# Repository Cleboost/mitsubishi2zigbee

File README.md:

# mitsubishi2zigbee

> [!CAUTION]
> **Early development - prototype only. Not production-ready.**
>
> This project is experimental and under active development. Firmware, wiring, and Zigbee behavior may change without notice. Bugs, incomplete features, and unexpected HVAC behavior are possible.
>
> **Do not rely on this device for critical climate control.** Use at your own risk. Test thoroughly before leaving it unattended.

Zigbee gateway firmware for Mitsubishi heat pumps and air conditioners with a **CN105** service port.

An **ESP32-C6** talks to the indoor unit over UART (CN105 protocol) and exposes it as a native Zigbee HVAC thermostat - no Wi-Fi or MQTT bridge on the microcontroller.

```
Home Assistant / Zigbee coordinator  ── Zigbee ──►  ESP32-C6  ── UART ──►  Mitsubishi unit
```

Inspired by [gysmo38/mitsubishi2MQTT](https://github.com/gysmo38/mitsubishi2MQTT), but uses Zigbee clusters (`hvacThermostat` + `hvacFanCtrl`) instead of MQTT.

## Features

| Category | Details |
| --- | --- |
| **Modes** | Off, Heat, Cool, Auto, Fan only, Dry |
| **Setpoint** | 16–31 °C in 0.5 °C steps |
| **Fan speed** | Auto, Quiet (Smart), Low, Medium, High |
| **Vane** | Auto, positions 1–5, Swing |
| **Telemetry** | Room temperature (unit sensor) |
| **Status LED** (WS2812) | Fast blue - scanning · Slow blue - network found, not paired · Green pulse - paired |

## Hardware

### Supported board

- [Waveshare ESP32-C6-Zero](https://www.waveshare.com/esp32-c6-zero.htm) (or any ESP32-C6 dev board with similar pinout)
- Built with **ESP-IDF** via **PlatformIO**

### CN105 wiring

The CN105 port provides 12 V, 5 V, and 5 V logic UART lines.

| CN105 pin | Signal | ESP32-C6 | Notes |
| --- | --- | --- | --- |
| 1 | 12 V | - | Do **not** use to power the ESP |
| 2 | GND | GND | Common ground |
| 3 | 5 V | 5 V / VBUS | Powers the ESP32-C6 |
| 4 | TX (unit → ESP) | GPIO 5 (UART RX) | 5 V logic - level shifted (5 V → 3.3 V) |
| 5 | RX (unit ← ESP) | GPIO 4 (UART TX) | 3.3 V logic - level shifted (3.3 V → 5 V) |

> **Warning:** Never feed 12 V into the ESP. Power the board from the CN105 5 V pin only.

## Build and flash

### Prerequisites

- [PlatformIO](https://platformio.org/) (VS Code extension or CLI)

### Commands

```bash
cd firmware
pio run --target upload    # build and flash
pio device monitor         # serial logs (115200 baud)
```

## Zigbee pairing

1. Flash the firmware and power the board from the CN105 port.
2. Put your Zigbee coordinator into pairing mode.
3. Watch the status LED:
   - Fast blue - searching for a network
   - Slow blue - network found, waiting to join
   - Green pulse - joined successfully
4. The device advertises as **`MZ-Zigbee-C6`** (vendor: Mitsubishi).

## Zigbee2MQTT integration

> **To write** - step-by-step setup guide coming soon.

A video tutorial will cover the full Zigbee2MQTT setup (external converter, `configuration.yaml`, pairing, and Home Assistant entities). Stay tuned.

In the meantime, the external converter source is already available in [`zigbee2mqtt_converter/mitsubishi_esp32c6.js`](zigbee2mqtt_converter/mitsubishi_esp32c6.js).

## Project layout

```
mitsubishi2zigbee/
├── hardware/                  # KiCad PCB (CN105 carrier for ESP32-C6-Zero)
├── firmware/                  # ESP-IDF / PlatformIO project
│   └── src/
│       ├── main.cpp           # Zigbee endpoint + status LED
│       └── cn105.cpp          # Mitsubishi CN105 UART driver
└── zigbee2mqtt_converter/     # Optional Z2M external converter

```

## License

See repository license file.

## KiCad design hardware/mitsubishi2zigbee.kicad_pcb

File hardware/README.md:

# Hardware

KiCad PCB for a [Waveshare ESP32-C6-Zero](https://www.waveshare.com/esp32-c6-zero.htm) carrier that plugs into a Mitsubishi **CN105** service port.

| Item | Details |
| --- | --- |
| MCU footprint | `Waveshare-ESP32:Waveshare-ESP32-C6-Zero_THT` (2×9 pin headers) |
| CN105 connector | `JST:JST_PA_B05B-PASK-1_1x05_P2.00mm_Vertical_CN105` |
| Level shifting | 5 V UART from the unit → 3.3 V for the ESP |

## CN105 UART wiring (rev 1 errata)

Mitsubishi CN105 pinout (viewed from the board):

| Pin | Signal | Direction (unit) |
| --- | --- | --- |
| 4 | TX | unit → ESP (ESP must **receive** here) |
| 5 | RX | ESP → unit (ESP must **transmit** here) |

**Rev 1 PCB bug:** pins 4 and 5 were swapped at the JST connector (ESP TX was routed to unit TX pin 4, ESP RX to unit RX pin 5). Symptom: yellow LED (Zigbee OK but CN105 silent), no UART traffic - no amount of firmware fixes this.

**Fix on assembled board:** cross **only** CN105 pins **4 ↔ 5** (swap the two UART wires on the cable or at `J1`). GND / 5 V unchanged.

Fixed in `mitsubishi2zigbee.kicad_pcb` for the next fabrication run.

## Open in KiCad

```bash
kicad hardware/mitsubishi2zigbee.kicad_pro
```

Project-specific symbol and footprint libraries live in `libs/`.

## Layout

```
hardware/
├── README.md
├── schematic.png
├── mitsubishi2zigbee.kicad_pro
├── mitsubishi2zigbee.kicad_sch
├── mitsubishi2zigbee.kicad_pcb
├── fp-lib-table
├── sym-lib-table
└── libs/
    ├── JST.pretty/
    ├── Waveshare-ESP32.pretty/
    └── Waveshare-ESP32.kicad_sym
```

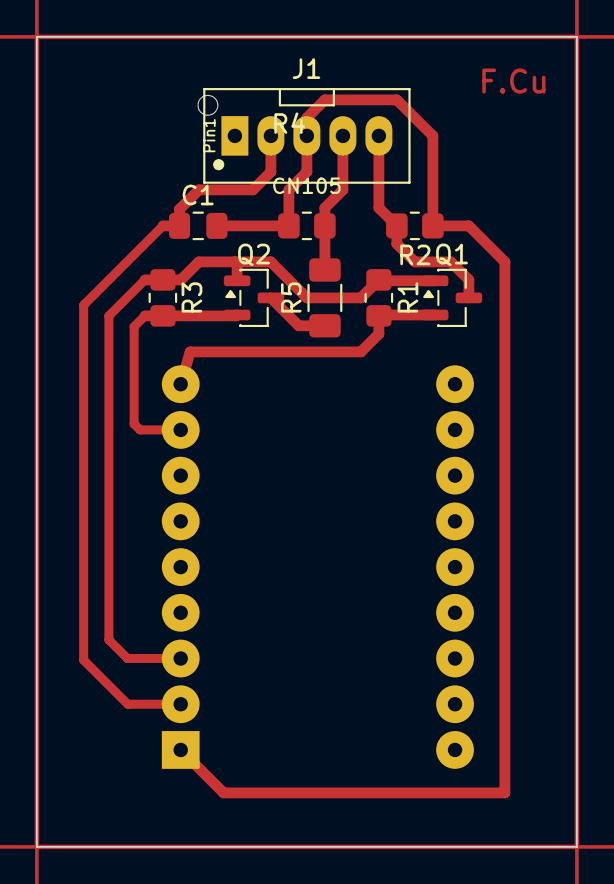
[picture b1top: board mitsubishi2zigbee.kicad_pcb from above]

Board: 2 copper layers, 30.0 x 45.0 mm, 10 parts (1 on the bottom side), 8 nets.

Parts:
C1: 10uF; C_0805_2012Metric_Pad1.18x1.45mm_HandSolder
J1: CN105; JST_PA_B05B-PASK-1_1x05_P2.00mm_Vertical_CN105
Q1, Q2: BSS138; SOT-23
R1, R2, R3, R4: 10K; R_0805_2012Metric_Pad1.20x1.40mm_HandSolder
R5: 0R; R_1206_3216Metric_Pad1.30x1.75mm_HandSolder
U1: ESP32-C6-Zero; Waveshare-ESP32-C6-Zero_THT

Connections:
+3V3: Q1.1 (G), Q2.1 (G), R1.1, R3.1, U1.3 (V3V)
/RX_3V3: Q1.2 (S), R1.2, U1.9 (IO5)
/RX_5V: J1.4, Q1.3 (D), R2.2
/TX_3V3: Q2.2 (S), R3.2, U1.8 (IO4)
/TX_5V: J1.5, R4.2, R5.2
GND: C1.1, J1.2, U1.2 (GND)
unnamed: Q2.3 (D), R5.1
VCC: C1.2, J1.3, R2.1, R4.1, U1.1 (VCC)
